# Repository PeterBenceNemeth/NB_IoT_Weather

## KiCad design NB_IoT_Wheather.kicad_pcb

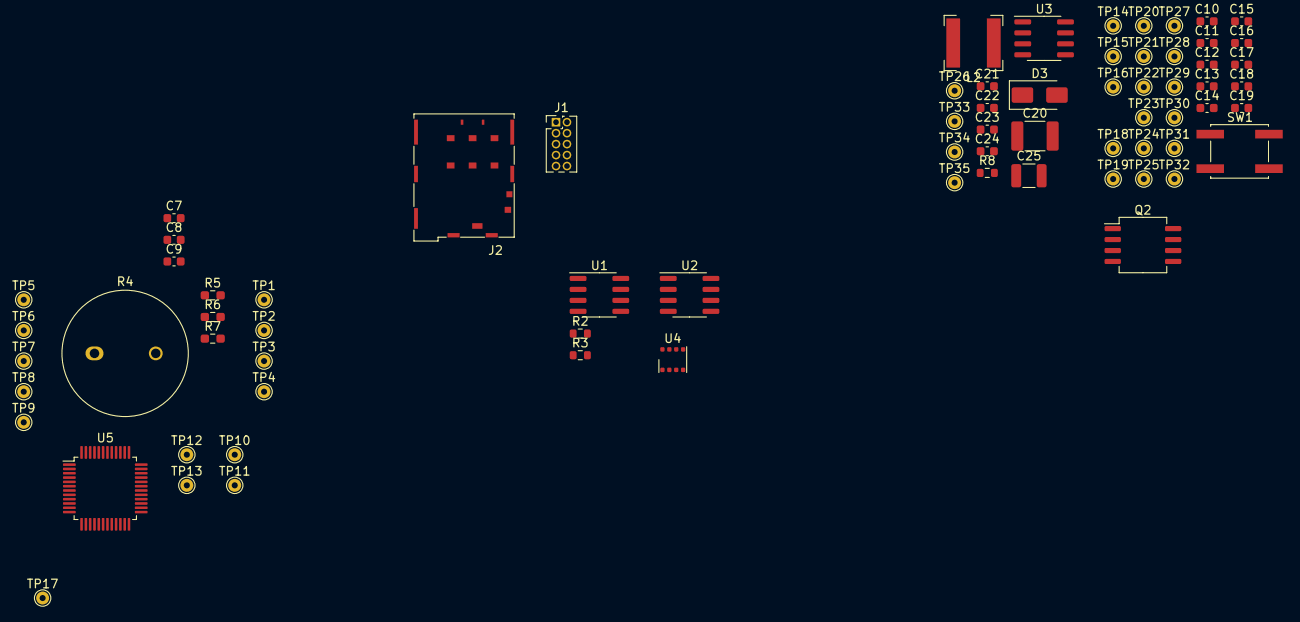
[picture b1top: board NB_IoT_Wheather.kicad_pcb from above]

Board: 2 copper layers, 72 parts (0 on the bottom side), 52 nets, no tracks yet.

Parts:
C7, C8, C9, C21: 10n; C_0603_1608Metric
C10, C11, C12, C13: 0,47u; C_0603_1608Metric
C14, C15, C16, C17, C18, C19, C22: 0,1u; C_0603_1608Metric
C20: 22u; C_1812_4532Metric
C23: 12nF; C_0603_1608Metric
C24: 120pF; C_0603_1608Metric
C25: 10u; C_1210_3225Metric
D3: B120-E3; D_SMA
J1: Conn_ARM_JTAG_SWD_10; PinHeader_2x05_P1.27mm_Vertical
J2: JAE_SIM_Card_SF72S006
L2: 15uH; L_Bourns-SRN6028
Q2: PMOS; SO-8_5.3x6.2mm_P1.27mm
R2, R3: 10k; R_0603_1608Metric
R4: R_Photo; TO-8-2
R5, R6, R7: 100k; R_0603_1608Metric_Pad0.98x0.95mm_HandSolder
R8: 3k74; R_0603_1608Metric
SW1: SW_Push; SW_SPST_EVQQ2
TP1, TP2, TP3, TP4, TP5, TP6, TP7, TP8, TP9, TP10, TP11, TP12, TP13, TP14, TP15, TP16, TP17, TP18, TP19, TP20, TP21, TP22, TP23, TP24, TP25, TP26, TP27, TP28, TP29, TP30, TP31, TP32, TP33, TP34, TP35: TestPoint; TestPoint_THTPad_D1.5mm_Drill0.7mm
U1: AT24CS32-SSHM; SOIC-8_3.9x4.9mm_P1.27mm
U2: BQ32000; SOIC-8_3.9x4.9mm_P1.27mm
U3: TPS5403; SOIC-8_3.9x4.9mm_P1.27mm
U4: BME680; Bosch_LGA-8_3x3mm_P0.8mm_ClockwisePinNumbering
U5: STM32F101C8Tx; LQFP-48_7x7mm_P0.5mm

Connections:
/EEPROM/GND: R2.2, U1.4 (GND), U1.7 (WP)
/EEPROM/SCL: TP11.1, U1.6 (SCL), U5.42 (PB6)
/EEPROM/SDA: TP10.1, U1.5 (SDA), U5.43 (PB7)
/EEPROM/VCC: R3.1, U1.8 (VCC)
/Irradiation Sensor/GND: C7.2, C8.2, R4.2, R7.2
/Irradiation Sensor/VDD: C8.1, C9.1, R5.1, R6.1
/Irradiation Sensor/V_Meas: C7.1, C9.2, R4.1, R5.2, R6.2, R7.1
/JTAG/GND: J1.3 (GND), J1.5 (GND), J1.9 (GNDDetect)
/MCU/GND: C10.2, C11.2, C12.2, C13.2, C14.2, C15.2, C16.2, C17.2, C18.2, C19.2, SW1.1, U5.8 (VSSA), U5.23 (VSS), U5.35 (VSS), U5.47 (VSS)
/MCU/I2C2.SCL: TP12.1, U2.6 (SCL), U5.21 (PB10)
/MCU/I2C2.SDA: TP13.1, U2.5 (SDA), U5.22 (PB11)
/MCU/JTAG.JNTRST: J1.10 (~RESET), TP5.1, U5.40 (PB4)
/MCU/JTAG.JTCK/SWCLK: J1.4 (SWCLK/TCK), TP6.1, U5.37 (PA14)
/MCU/JTAG.JTDI: J1.8 (NC/TDI), TP9.1, U5.38 (PA15)
/MCU/JTAG.JTDO: J1.6 (SWO/TDO), TP8.1, U5.39 (PB3)
/MCU/JTAG.JTMS/SWDIO: J1.2 (SWDIO/TMS), TP7.1, U5.34 (PA13)
/MCU/NRST: C19.1, SW1.2, U5.7 (NRST)
/MCU/PA0: TP14.1, U5.10 (PA0)
/MCU/PA1: TP15.1, U5.11 (PA1)
/MCU/PA2: TP16.1, U5.12 (PA2)
/MCU/PA3: TP17.1, U5.13 (PA3)
/MCU/PA8: TP18.1, U5.29 (PA8)
/MCU/PA9: TP19.1, U5.30 (PA9)
/MCU/PA10: TP20.1, U5.31 (PA10)
/MCU/PA11: TP21.1, U5.32 (PA11)
/MCU/PA12: TP22.1, U5.33 (PA12)
/MCU/PB0: TP23.1, U5.18 (PB0)
/MCU/PB1: TP24.1, U5.19 (PB1)
/MCU/PB5: TP25.1, U5.41 (PB5)
/MCU/PB8: TP31.1, U5.45 (PB8)
/MCU/PB9: TP32.1, U5.46 (PB9)
/MCU/PB12: TP27.1, U5.25 (PB12)
/MCU/PB13: TP28.1, U5.26 (PB13)
/MCU/PB14: TP29.1, U5.27 (PB14)
/MCU/PB15: TP30.1, U5.28 (PB15)
/MCU/SPI1.MISO: TP1.1, U4.5 (SDO), U5.16 (PA6)
/MCU/SPI1.MOSI: TP3.1, U4.3 (SDI), U5.17 (PA7)
/MCU/SPI1.NSS: TP4.1, U4.2 (CSB), U5.14 (PA4)
/MCU/SPI1.SCK: TP2.1, U4.4 (SCK), U5.15 (PA5)
/MCU/VBAT: C10.1, C11.1, C14.1, U5.1 (VBAT)
/MCU/VCC: C12.1, C13.1, C15.1, C16.1, C17.1, C18.1, U5.9 (VDDA), U5.24 (VDD), U5.36 (VDD), U5.48 (VDD)
/PSU/3V3: C20.2, D3.1 (K), L2.2, TP35.1
/PSU/GND: C20.1, C21.2, C23.2, C24.2, C25.1, D3.2 (A), U3.7 (GND)
/PSU/VIN: C25.2, TP26.1, U3.2 (VIN)
/Temperature Sensor/GND: U4.1 (GND), U4.7 (GND)
unnamed: C23.1, R8.2
unnamed: R3.2, U1.1 (A0)
unnamed: R2.1, U1.2 (A1), U1.3 (A2)
unnamed: C22.2, TP34.1, U3.1 (BOOT)
unnamed: C24.1, R8.1, U3.6 (COMP)
unnamed: C22.1, L2.1, TP33.1, U3.8 (LX)
unnamed: C21.1, U3.4 (SS)

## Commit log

2024-04-23 Ongoing dev 0.1
    Not finished initial schematic
